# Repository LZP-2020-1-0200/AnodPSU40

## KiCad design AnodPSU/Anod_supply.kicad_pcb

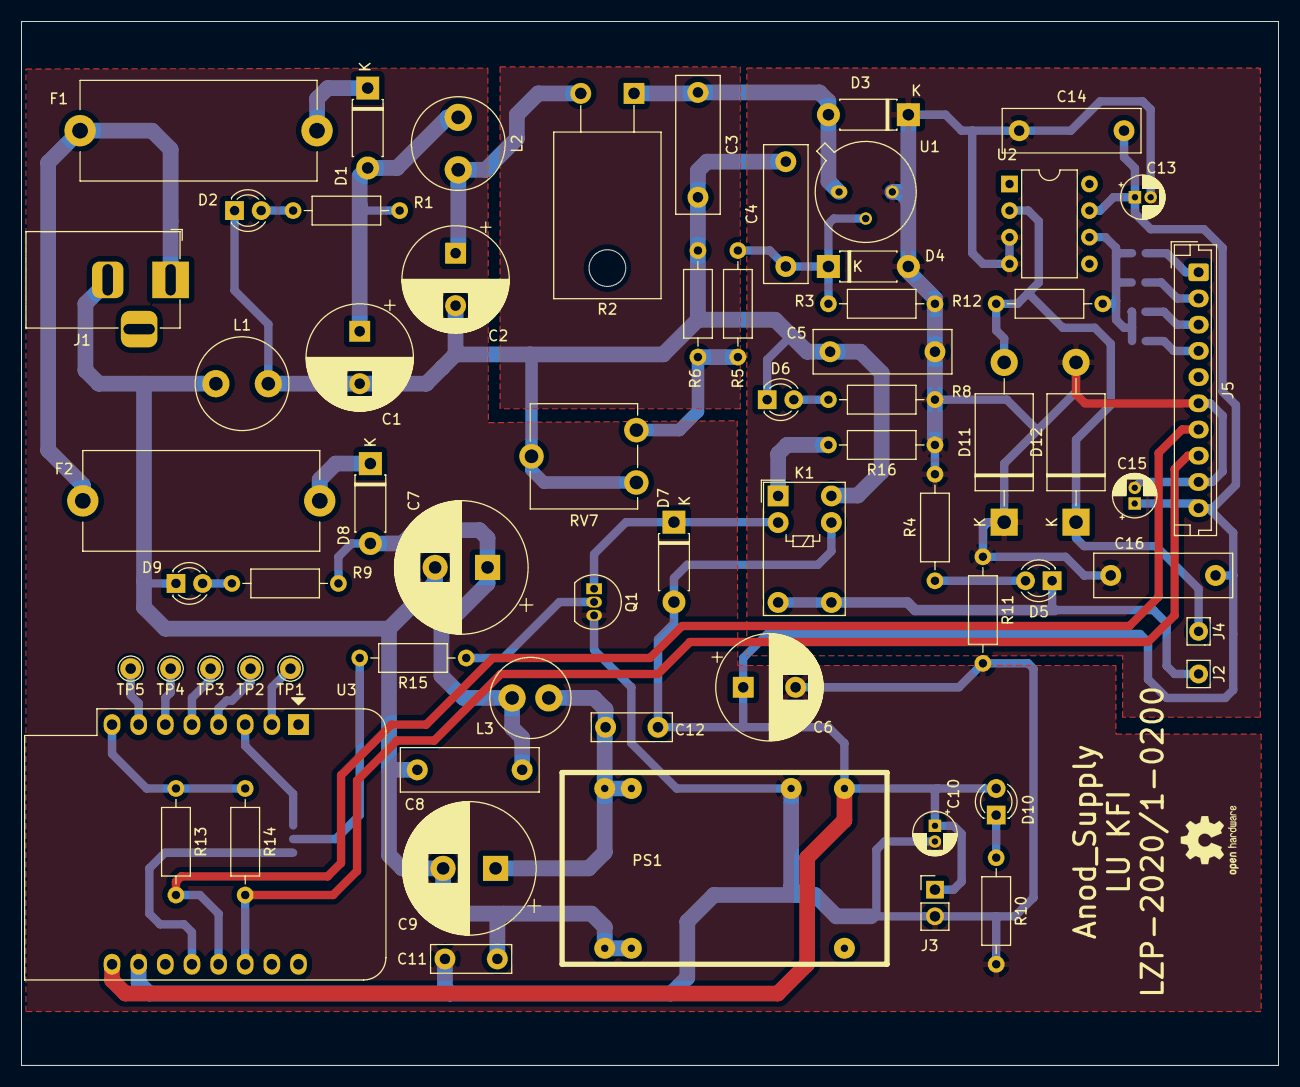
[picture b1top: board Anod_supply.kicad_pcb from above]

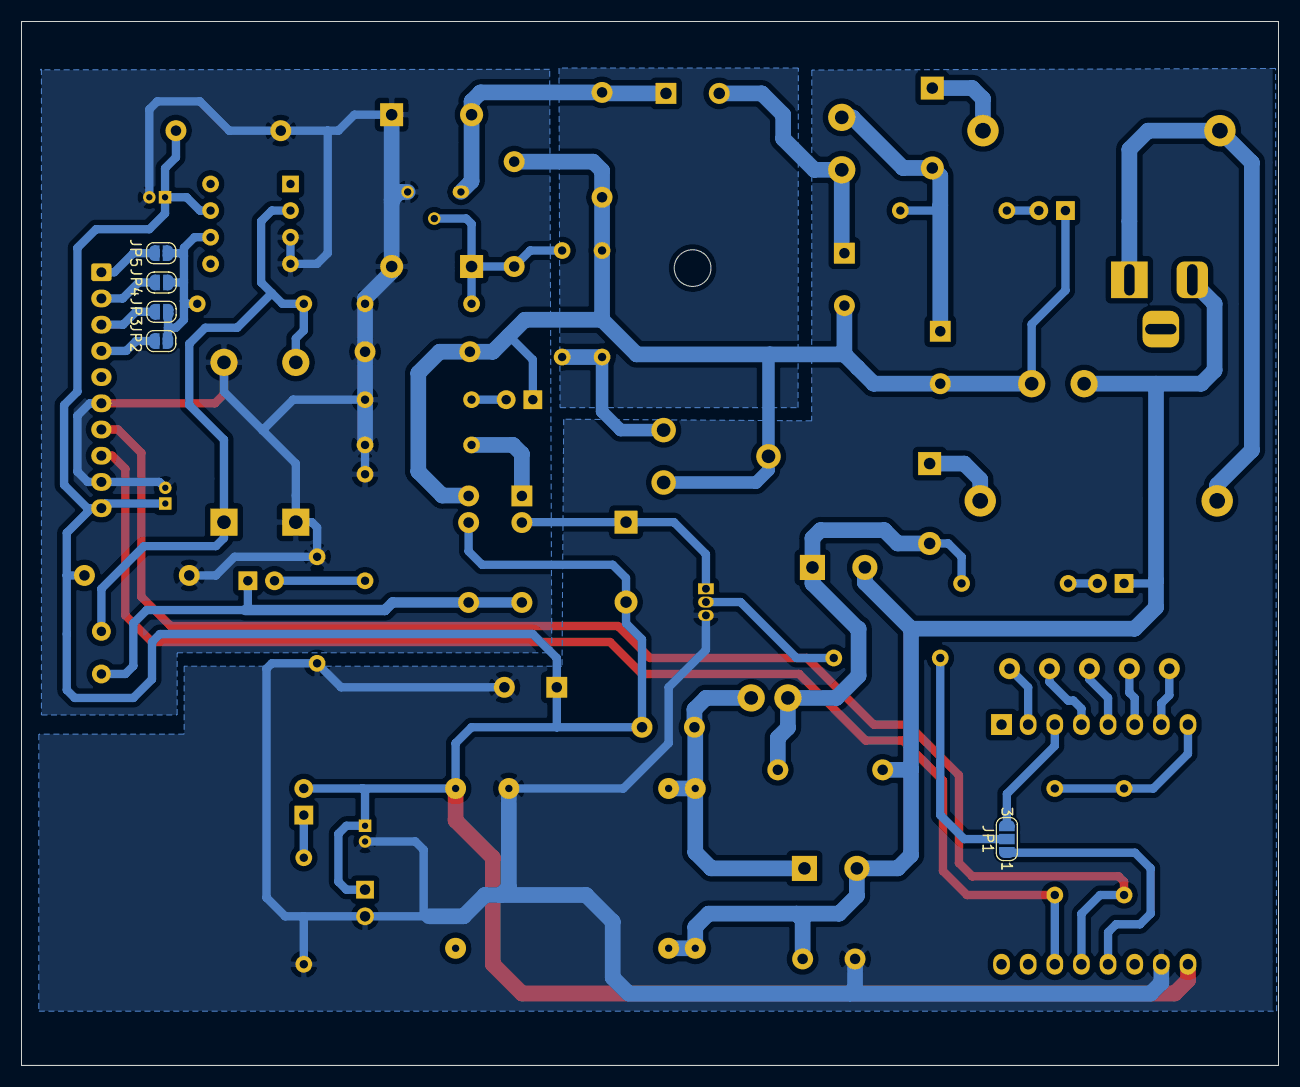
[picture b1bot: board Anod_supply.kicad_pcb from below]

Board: 2 copper layers, 119.9 x 99.6 mm, 70 parts (5 on the bottom side), 41 nets.

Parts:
C1, C2: 100uF/100V; CP_Radial_D10.0mm_P5.00mm
C3, C5, C8: 1uF/100V; C_Rect_L13.0mm_W4.0mm_P10.00mm_FKS3_FKP3_MKS4
C4, C14, C16: 2,2uF; C_Rect_L13.0mm_W4.0mm_P10.00mm_FKS3_FKP3_MKS4
C6: 330uF/10V; CP_Radial_D10.0mm_P5.00mm
C7, C9: 330uF/100V; CP_Radial_D12.5mm_P5.00mm
C10, C13, C15: 10uF/16V; CP_Radial_D4.0mm_P1.50mm
C11, C12: 1nF/2KV; C_Disc_D7.5mm_W2.5mm_P5.00mm
D1, D3, D4, D7, D8: IN4007; D_DO-41_SOD81_P7.62mm_Horizontal
D2, D5, D6, D9, D10: LED; LED_D3.0mm
D11, D12: SB3100; D_DO-201AE_P15.24mm_Horizontal
F1, F2: Fuse; Fuseholder_Cylinder-5x20mm_Stelvio-Kontek_PTF78_Horizontal_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
J1: Barrel_Jack_Switch; BarrelJack_Horizontal
J2: Cathode; Pin_D0.9mm_L10.0mm_W2.4mm_FlatFork
J3: Conn_01x02; PinHeader_1x02_P2.54mm_Vertical
J4: Anode; Pin_D0.9mm_L10.0mm_W2.4mm_FlatFork
J5: ads1115_connector; JST_EH_B10B-EH-A_1x10_P2.50mm_Vertical
JP1: SolderJumper_3_Open; SolderJumper-3_P1.3mm_Open_RoundedPad1.0x1.5mm_NumberLabels
JP2, JP3, JP4, JP5: SolderJumper_2_Open; SolderJumper-2_P1.3mm_Open_RoundedPad1.0x1.5mm
K1: G5V-1; Relay_SPDT_Omron_G5V-1
L1, L2: 1mH; L_Radial_D8.7mm_P5.00mm_Fastron_07HCP
L3: 4.7uH; L_Radial_D7.5mm_P3.50mm_Fastron_07P
PS1: MPRB4805
Q1: BC547; TO-92_Inline
R1, R4, R8, R9, R10: 47K; R_Axial_DIN0207_L6.3mm_D2.5mm_P10.16mm_Horizontal
R2: 150/18W; TO-220-2_Horizontal_TabDown
R3: 240; R_Axial_DIN0207_L6.3mm_D2.5mm_P10.16mm_Horizontal
R5: 6K8; R_Axial_DIN0207_L6.3mm_D2.5mm_P10.16mm_Horizontal
R6: 2K2; R_Axial_DIN0207_L6.3mm_D2.5mm_P10.16mm_Horizontal
R11, R16: 0R; R_Axial_DIN0207_L6.3mm_D2.5mm_P10.16mm_Horizontal
R12, R15: 1K; R_Axial_DIN0207_L6.3mm_D2.5mm_P10.16mm_Horizontal
R13, R14: 10K; R_Axial_DIN0207_L6.3mm_D2.5mm_P10.16mm_Horizontal
RV7: 2K2; Potentiometer_ACP_CA9-V10_Vertical
TP1: TestPoint; TestPoint_THTPad_D2.0mm_Drill1.0mm
TP2, TP3, TP4, TP5: TP; TestPoint_THTPad_D2.0mm_Drill1.0mm
U1: LM317_TO39; TO-39-3
U2: MCP601-xP; DIP-8_W7.62mm
U3: WeMos_D1_mini; WEMOS_D1_mini_light

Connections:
+5V: C6.1, C10.1, C12.1, C13.1, C14.2, C15.1, C16.2, D7.2, D10.2, J3.1, J5.10, K1.9, PS1.14, U2.7, U3.9
/REL_TR: Q1.2, R15.1
/SCL: J5.8, R14.2, U3.14
/SDA: J5.7, R13.2, U3.13
GNDA: C5.1, C13.2, C14.1, C15.2, C16.1, D3.1, D4.2, D11.1, D12.2, J5.6, J5.9, R3.1, R4.2, R8.2, R11.1, R16.1, U1.3, U2.3, U2.4
GNDD: C6.2, C10.2, C11.2, J3.2, PS1.16, Q1.3, R10.2, R11.2, U3.10
unnamed: C1.1, D1.2, L2.1, R1.1
unnamed: C1.2, C2.2, C3.2, C4.2, C5.2, D2.1, D6.1, K1.10, L1.2, R6.1, RV7.2, RV7.3
unnamed: C2.1, L2.2, R2.2
unnamed: C3.1, D3.2, R2.1, U1.1
unnamed: C4.1, D4.1, R3.2, R5.2, U1.2
unnamed: C7.1, C8.1, D8.2, L3.1, R9.1
unnamed: C7.2, C8.2, C9.2, C11.1, D9.1, J1.2, L1.1, PS1.2, PS1.3
unnamed: C9.1, C12.2, L3.2, PS1.22, PS1.23
unnamed: D1.1, F1.1
unnamed: D2.2, R1.2
unnamed: D5.1, J2.1, K1.5, K1.6
unnamed: D5.2, R4.1
unnamed: D6.2, R8.1
unnamed: D7.1, K1.2, Q1.1
unnamed: D8.1, F2.1
unnamed: D9.2, R9.2
unnamed: D10.1, R10.1
unnamed: D11.2, D12.1, J4.1, R12.1, U2.2
unnamed: F1.2, F2.2, J1.1
unnamed: J5.1, JP5.2
unnamed: J5.2, JP4.2
unnamed: J5.3, JP3.2
unnamed: J5.4, JP2.2
unnamed: JP1.1, U3.12
unnamed: JP1.2, R15.2
unnamed: JP1.3, U3.3
unnamed: JP2.1, JP3.1, JP4.1, JP5.1, R12.2, U2.6
unnamed: K1.1, R16.2
unnamed: R5.1, R6.2, RV7.1
unnamed: R13.1, R14.1, U3.8
unnamed: TP1.1, U3.2
unnamed: TP2.1, U3.4
unnamed: TP3.1, U3.5
unnamed: TP4.1, U3.6
unnamed: TP5.1, U3.7

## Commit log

2022-06-14 Schematics and PCB update
2022-06-20 Replaced response with JSON
2023-08-07 added software src
